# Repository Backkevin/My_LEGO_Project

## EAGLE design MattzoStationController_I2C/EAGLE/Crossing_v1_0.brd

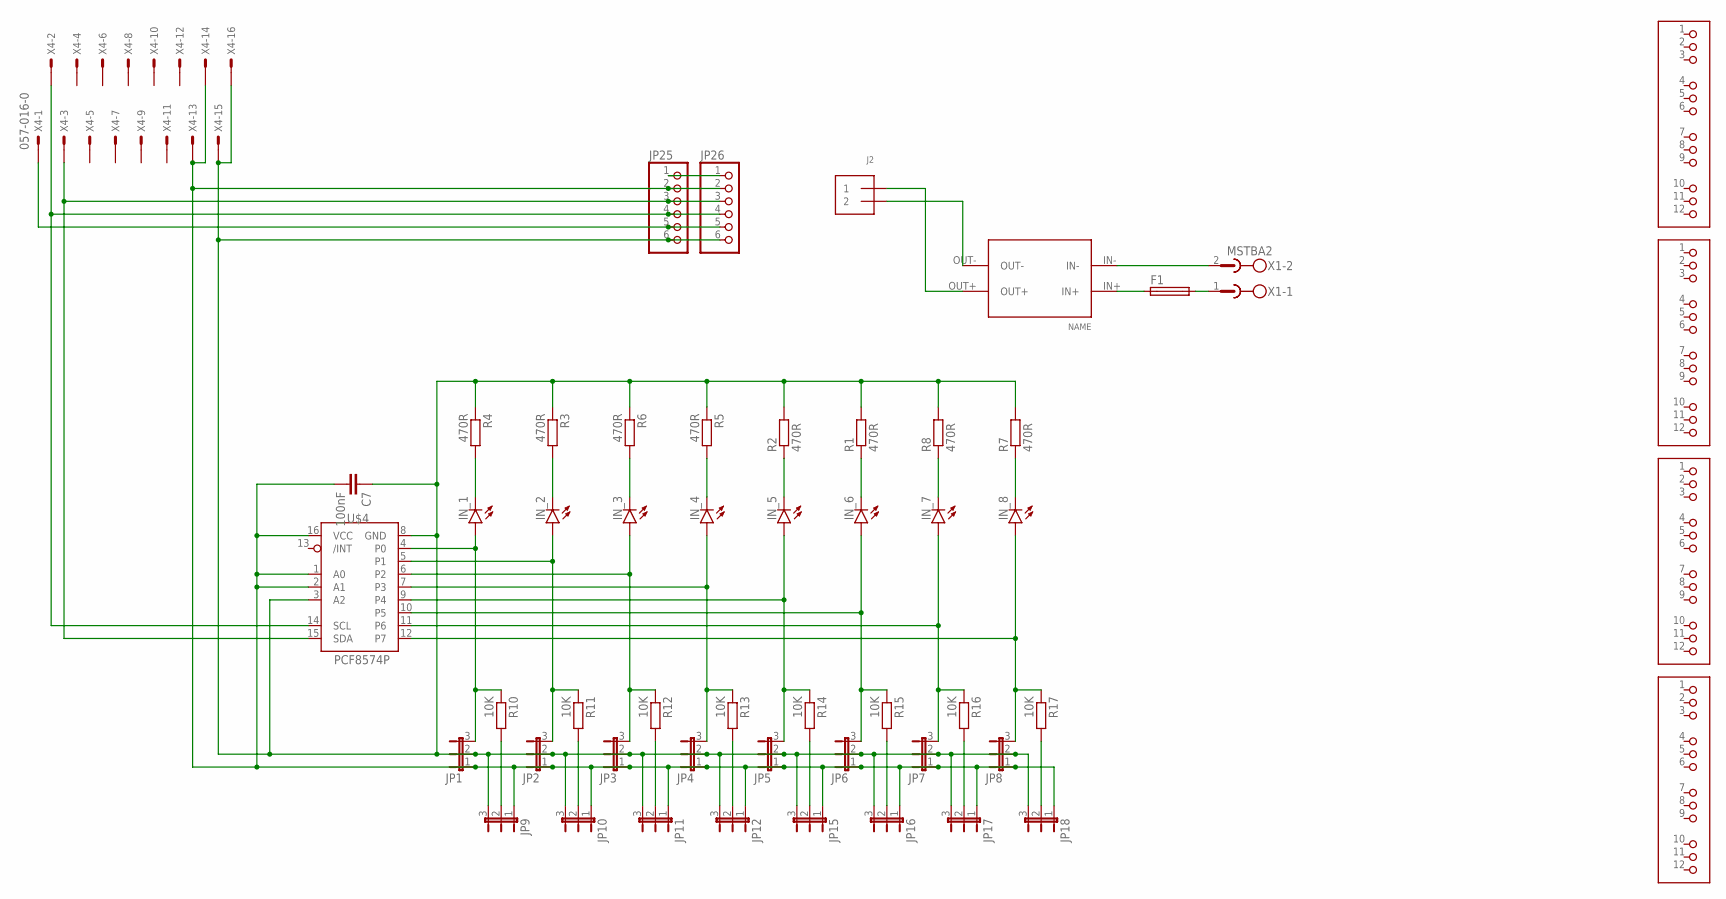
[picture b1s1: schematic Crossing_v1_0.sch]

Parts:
C7: 100nF; C025-024X044
F1: SH25
IN_1, IN_2, IN_3, IN_4, IN_5, IN_6, IN_7, IN_8: LED3MM
J2: TERMBLOCK_1X2; TERMBLOCK_1X2-3.5MM
JP1, JP2, JP3, JP4, JP5, JP6, JP7, JP8, JP9, JP10, JP11, JP12, JP15, JP16, JP17, JP18: JP2E; JP2
JP25, JP26: PINHD-1X6CB; 1X06-CLEANBIG
JP27, JP28, JP29, JP30: HEADER-3X04; 3X04
R1, R2, R3, R4, R5, R6, R7, R8: 470R; 0309/10
R10, R11, R12, R13, R14, R15, R16, R17: 10K; 0309/10
U$2: CP8-ADJ
U$4: PCF8574P; DIL16
X1: MSTBA2
X4: 057-016-0

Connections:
unnamed: J2.2, U$2.OUT-
unnamed: J2.1, U$2.OUT+
unnamed: JP25.4, JP26.4, U$4.14 (SCL), X4.2
unnamed: JP25.5, JP26.5, X4.1
unnamed: C7.1, JP1.2, JP2.2, JP3.2, JP4.2, JP5.2, JP6.2, JP7.2, JP8.2, JP9.3, JP10.3, JP11.3, JP12.3, JP15.3, JP16.3, JP17.3, JP18.3, JP25.6, JP26.6, R1.2, R2.2, R3.1, R4.1, R5.1, R6.1, R7.2, R8.2, U$4.3 (A2), U$4.8 (GND), X4.15, X4.16
unnamed: JP25.1, JP26.1
unnamed: C7.2, JP1.1, JP2.1, JP3.1, JP4.1, JP5.1, JP6.1, JP7.1, JP8.1, JP9.1, JP10.1, JP11.1, JP12.1, JP15.1, JP16.1, JP17.1, JP18.1, JP25.2, JP26.2, U$4.1 (A0), U$4.2 (A1), U$4.16 (VCC), X4.13, X4.14
unnamed: U$2.IN-, X1.2
unnamed: F1.1, U$2.IN+
unnamed: F1.2, X1.1
unnamed: JP25.3, JP26.3, U$4.15 (SDA), X4.3
unnamed: IN_8.K (C), R7.1
unnamed: IN_7.K (C), R8.1
unnamed: IN_6.K (C), R1.1
unnamed: IN_5.K (C), R2.1
unnamed: IN_4.K (C), R5.2
unnamed: IN_3.K (C), R6.2
unnamed: IN_2.K (C), R3.2
unnamed: IN_1.K (C), R4.2
unnamed: IN_1.A, JP1.3, R10.1, U$4.4 (P0)
unnamed: IN_2.A, JP2.3, R11.1, U$4.5 (P1)
unnamed: IN_3.A, JP3.3, R12.1, U$4.6 (P2)
unnamed: IN_4.A, JP4.3, R13.1, U$4.7 (P3)
unnamed: IN_5.A, JP5.3, R14.1, U$4.9 (P4)
unnamed: IN_6.A, JP6.3, R15.1, U$4.10 (P5)
unnamed: IN_7.A, JP7.3, R16.1, U$4.11 (P6)
unnamed: IN_8.A, JP8.3, R17.1, U$4.12 (P7)
unnamed: JP9.2, R10.2
unnamed: JP10.2, R11.2
unnamed: JP11.2, R12.2
unnamed: JP12.2, R13.2
unnamed: JP15.2, R14.2
unnamed: JP16.2, R15.2
unnamed: JP17.2, R16.2
unnamed: JP18.2, R17.2

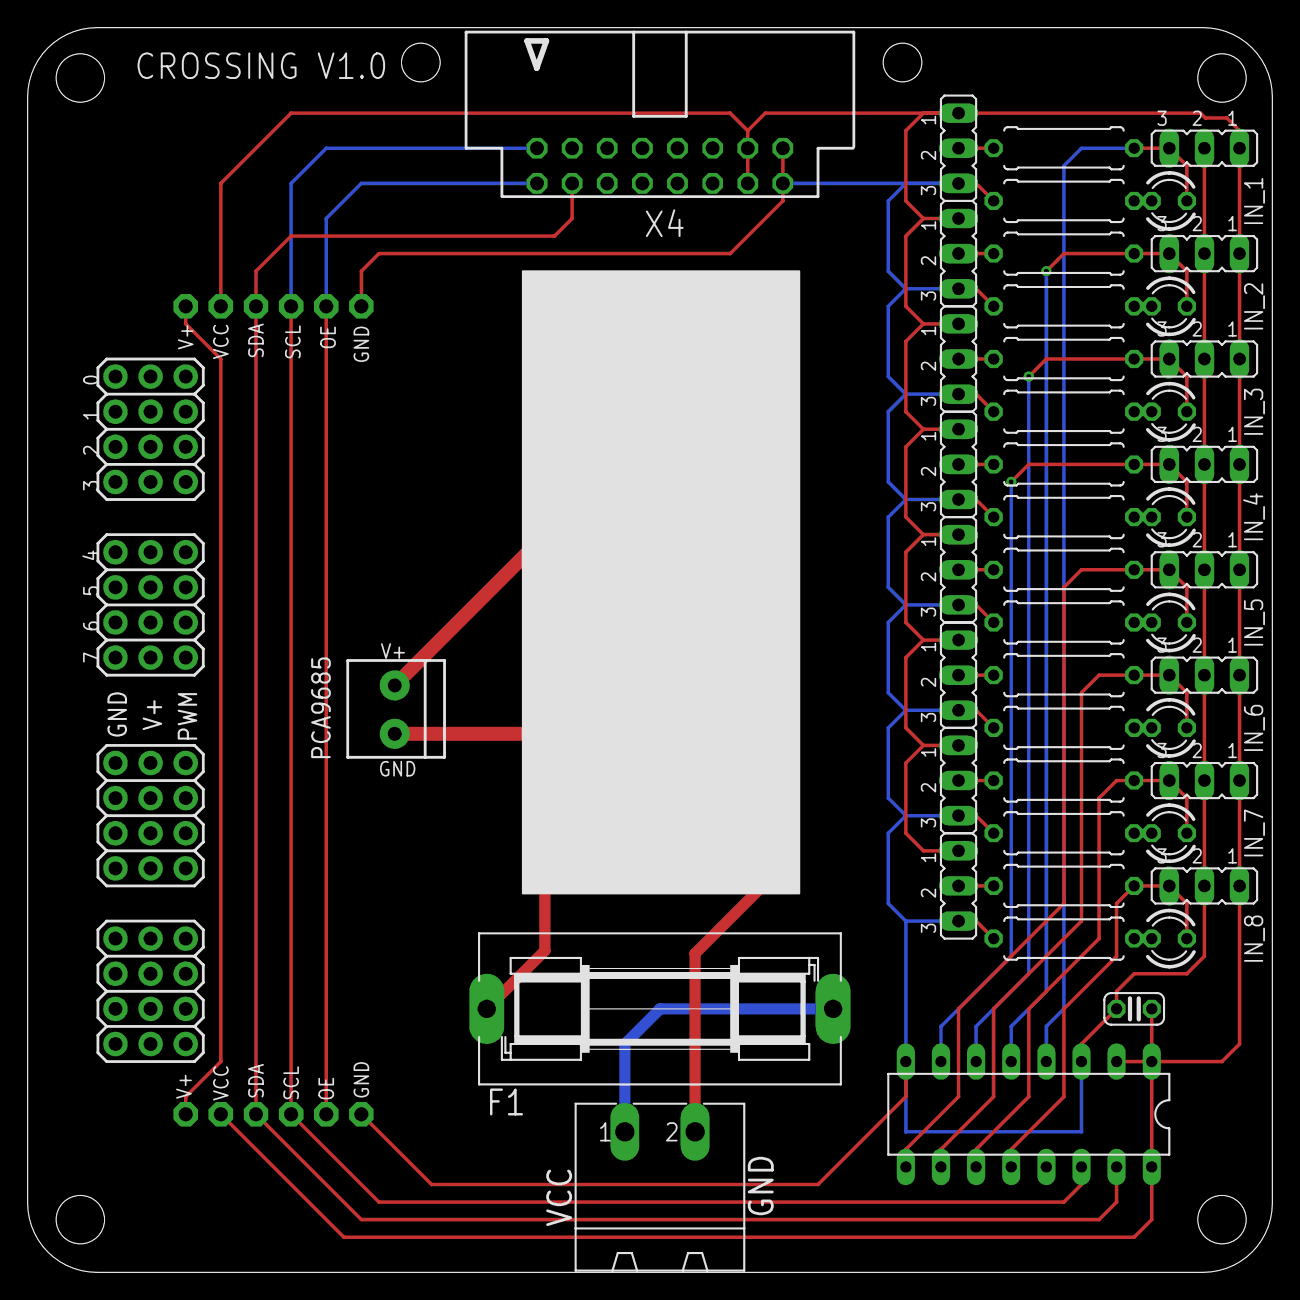
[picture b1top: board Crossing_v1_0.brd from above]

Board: 2 copper layers, 90.0 x 90.0 mm, 53 parts (0 on the bottom side), 35 nets.

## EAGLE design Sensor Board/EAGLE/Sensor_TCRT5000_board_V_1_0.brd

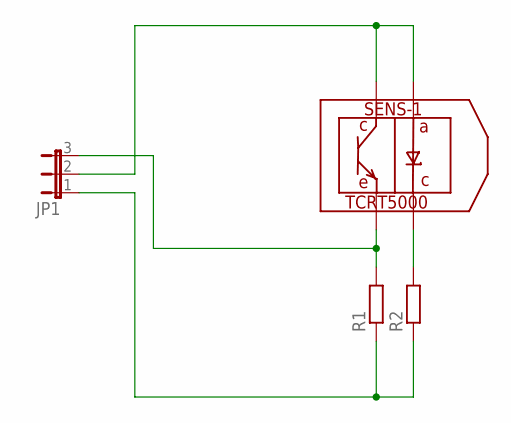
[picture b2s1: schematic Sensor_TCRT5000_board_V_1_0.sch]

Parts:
JP1: JP2E; JP2
R1, R2: R-EU_0309/10; 0309/10
SENS-1: TCRT5000; 5000

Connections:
unnamed: JP1.2, SENS-1.P$1, SENS-1.P$3
unnamed: JP1.1, R1.1, R2.1
unnamed: R2.2, SENS-1.P$4
unnamed: JP1.3, R1.2, SENS-1.P$2

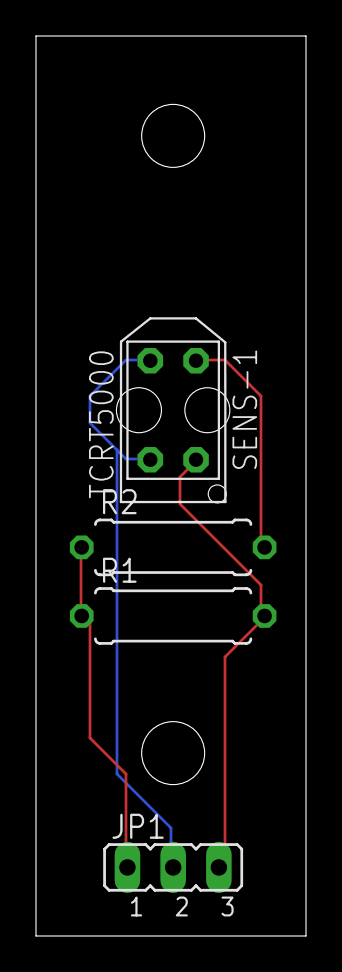
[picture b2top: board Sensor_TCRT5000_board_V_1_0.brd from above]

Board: 2 copper layers, 15.0 x 50.0 mm, 4 parts (0 on the bottom side), 4 nets.

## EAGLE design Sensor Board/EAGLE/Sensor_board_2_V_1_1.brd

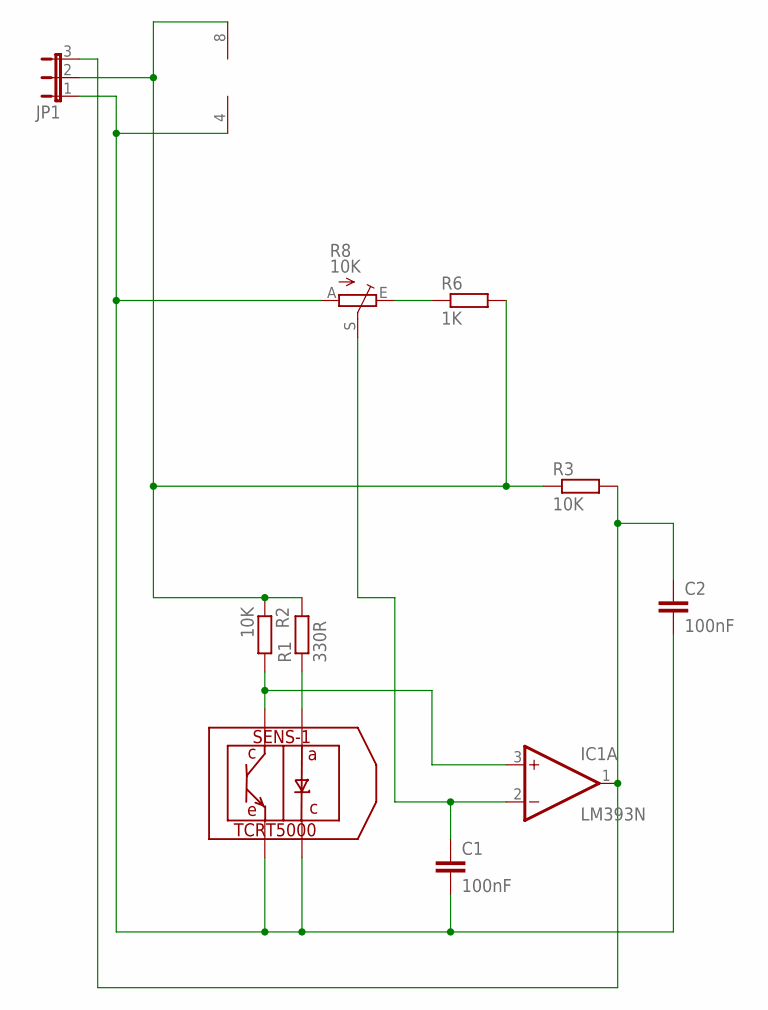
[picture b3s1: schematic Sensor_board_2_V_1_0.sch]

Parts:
C1, C2: 100nF; C025_050-025X075
IC1: LM393N; DIL08
JP1: JP2E; JP2
R1: 330R; 0309/10
R2, R3: 10K; 0309/10
R6: 1K; 0309/10
R8: 10K; B64Y
SENS-1: TCRT5000; 5000

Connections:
unnamed: IC1.8 (V+), JP1.2, R1.2, R2.1, R3.1, R6.2
unnamed: C1.2, C2.2, IC1.4 (V-), JP1.1, R8.A, SENS-1.P$2, SENS-1.P$4
unnamed: R1.1, SENS-1.P$3
unnamed: IC1.3 (+IN), R2.2, SENS-1.P$1
unnamed: C2.1, IC1.1 (OUT), JP1.3, R3.2
unnamed: R6.1, R8.E
unnamed: C1.1, IC1.2 (-IN), R8.S

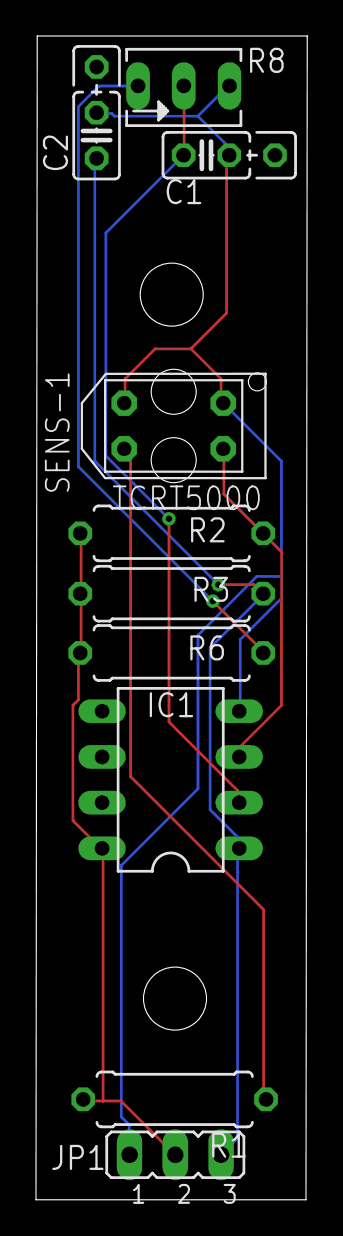
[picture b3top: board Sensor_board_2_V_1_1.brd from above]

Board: 2 copper layers, 15.1 x 64.7 mm, 10 parts (0 on the bottom side), 7 nets.
